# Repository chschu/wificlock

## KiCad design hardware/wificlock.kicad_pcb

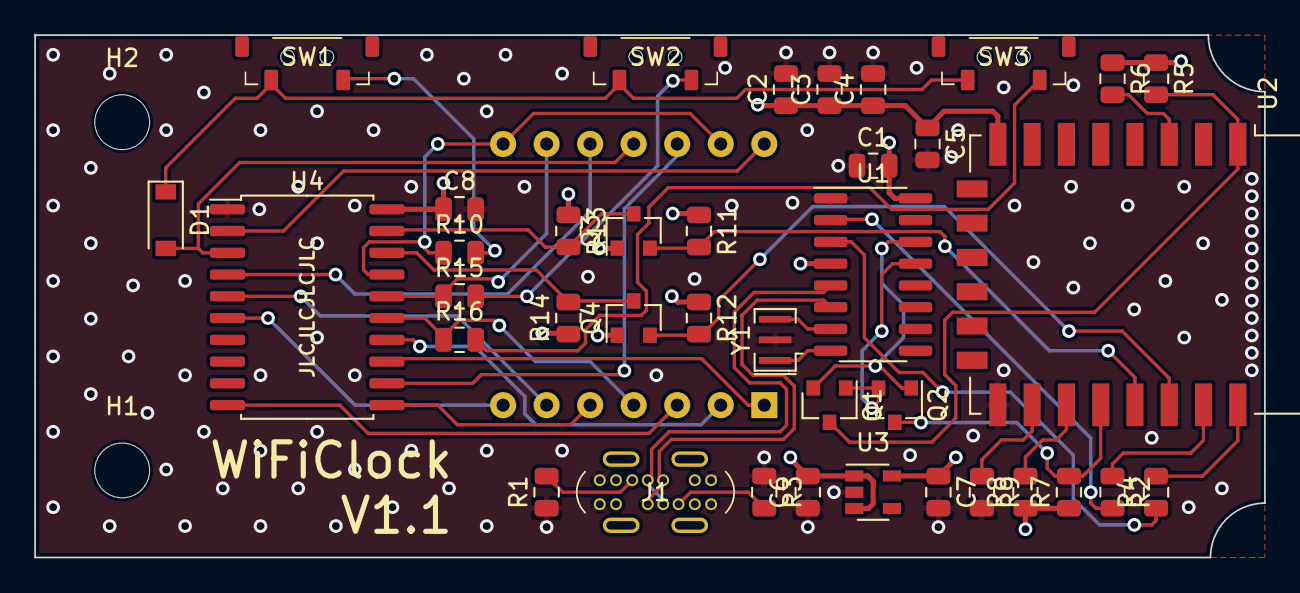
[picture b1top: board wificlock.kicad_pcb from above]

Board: 4 copper layers, 71.8 x 30.5 mm, 41 parts (1 on the bottom side), 41 nets.

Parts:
C1, C5, C8: 100n; C_0805_2012Metric
C2, C3, C4: 10u; C_0805_2012Metric
C6, C7: 1u; C_0805_2012Metric
D1: 1N4148W; D_SOD-123
H1, H2: MountingHole; MountingHole_3.2mm_M3_ISO14580
J1: USB_C_Receptacle_USB2.0; USB_C_Receptacle_UT03FD014SX01ZA_Vertical
Q1, Q2, Q3, Q4: AO3402; SOT-23
R1, R3: 5k1; R_0805_2012Metric
R2, R4: 470; R_0805_2012Metric
R5, R6, R7, R8, R9: 10k; R_0805_2012Metric
R10, R15, R16: 47k; R_0805_2012Metric
R11, R12, R13, R14: 4k7; R_0805_2012Metric
SW1, SW2, SW3: SW_SPST; SW_SPST_SMD_3x6x3.5_Side
U1: CH340C/G; SOIC-16_3.9x9.9mm_P1.27mm
U2: ESP-12F; ESP-12E
U3: ME6211C33M5G; SOT-23-5
U4: HT16K33-20SOP; SOIC-20W_7.5x12.8mm_P1.27mm
U5: KW4-56NCLB-P; CL5643AH
Y1: 12MHz; Resonator_SMD_muRata_CSTxExxV-3Pin_3.0x1.1mm

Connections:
+3V3: C1.2, C2.1, C3.1, C4.1, C5.1, C7.1, Q3.1, Q4.1, R5.1, R6.1, R7.1, R8.1, R11.1, R12.1, U1.4, U1.16, U2.8, U3.5
+5V: C6.2, C8.1, J1.A4, J1.A9, J1.B4, J1.B9, R13.1, R14.1, U3.1, U3.3, U4.20
COM0: U4.2, U5.14
COM1: D1.2, U4.3, U5.11
COM2: U4.4, U5.10
COM3: U4.5, U5.6
COM4: U4.6, U5.7
D+: J1.A6, J1.B6, U1.5
D-: J1.A7, J1.B7, U1.6
EN: R6.2, U2.3
GND: C1.1, C2.2, C3.2, C4.2, C5.2, C6.1, C7.2, C8.2, J1.A1, J1.A12, J1.B1, J1.B12, R1.1, R3.1, R9.2, U1.1, U2.15, U3.2, U4.1, Y1.2
GPIO0: Q2.3, R7.2, U2.18
GPIO2: R8.2, U2.17
GPIO15: R9.1, U2.16
K1: R10.1, U4.17, U5.8, U5.13
K2: R15.1, U4.16, U5.9
K3: R16.1, U4.15, U5.4
unnamed: D1.1, SW1.1, SW2.1, SW3.1
unnamed: J1.A5, R1.2
unnamed: J1.B5, R3.2
unnamed: R2.2, U1.2
unnamed: R4.1, U1.3
unnamed: R10.2, SW1.2
unnamed: R15.2, SW2.2
unnamed: R16.2, SW3.2
unnamed: U1.7, Y1.3
unnamed: U1.8, Y1.1
ROW3: U4.14, U5.2
ROW4: U4.13, U5.1
ROW5: U4.12, U5.12
ROW6: U4.11, U5.5
ROW7: U4.10, U5.3
RXD: R2.1, U2.21
SCL5: Q4.3, R14.2, U4.18
SCL33: Q4.2, R12.2, U2.20
SDA5: Q3.3, R13.2, U4.19
SDA33: Q3.2, R11.2, U2.19
TXD: R4.2, U2.22
~DTR: Q1.1, Q2.2, U1.13
~RST: Q1.3, R5.2, U2.1
~RTS: Q1.2, Q2.1, U1.14

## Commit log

2021-01-02 initial firmware version for WiFi clock with captive portal for config
2021-01-02 use references for DNS and web server in captive config
2021-01-05 remove unused variables and includes, change CLK and DIO pins
2021-01-08 remove serial output, generalize upload port
2021-01-08 increase bit rate for TM1637 (after desoldering too large capacitors)
2021-01-08 update display only if segments changed
2021-01-11 switch to TM16xx library that supports reading keys
2021-02-14 check if header has already been included
2021-02-15 use more intuitive LED mapping that also works for 20-pin variant of HT16K33
2021-02-15 switch to HT16K33 with CL5643AH display
2021-02-15 add schematic
2021-02-28 add footprints for display and tactile side switch
2021-02-28 add key handling to HT16K33, extract seven-segment mappings to separate class
2021-03-25 extract button and display state handling to class
2021-03-27 fix i2c_read and buffer size
2021-03-30 add datasheet for USB receptacle
2021-03-30 add pcb and footprints
2021-03-30 manually route IC decoupling and some other critical traces
2021-03-31 autoroute and small manual routing fixes
2021-03-31 use correct diode model
2021-03-31 add order number marker for JLCPCB
2021-03-31 via stitching
2021-03-31 some more minor routing fixes
2021-03-31 change via and pad hole sizes to 0.45 mm to match JLCPCB production
2021-03-31 add Gerber files for V1.0
2021-04-02 extract display update and key handling to WiFiClock class
2021-04-03 use snake_case for variables
2021-04-04 add datasheet for AO3402
2021-04-04 rename datasheet for USB receptacle
2021-04-05 add 3D models for footprints
2021-04-06 update KiCad
2021-04-07 update platform
2021-04-16 fix display footprint to match actual hardware (only changes silkscreen on PCB)
2021-04-17 allow registration of multiple key handlers, pass key index to handler instead of column and row
2021-04-18 fix case fallbck
2021-04-21 implement AppController and separate apps to cycle through
2021-04-22 add virtual destructors (never called at the moment)
2021-04-22 enable access point if all three buttons are pressed during startup, enable station mode otherwise (AP is unstable while STA is scanning channels for its configured network)
2021-04-22 fix fallback return value
2021-04-26 move components to align (center) display, USB receptacle and switches; minor routing optimizations; update Gerber files
2021-04-29 remove no longer required event handler
2021-05-06 rename ap_mode to config_mode, disable DNS and web server when not in config mode
2021-05-06 change to generic board
2021-05-23 fix include
2021-05-23 generalize serial port device path
2021-05-23 setup access point (takes almost a second on some chips) before starting display to avoid unresponsive delay
2021-05-23 add STEP file for case (includes PCB)
2022-02-20 implement versioned EEPROM format
2022-02-20 add hostname configuration option
2022-02-20 update platform, use LWIP2 with IPv6 support, use NonOS SDK 3
2022-12-04 update files after KiCad update
2022-12-04 enable config mode display for fresh device, set default full brightness
